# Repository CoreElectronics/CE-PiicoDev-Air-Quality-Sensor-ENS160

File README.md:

# PiicoDev® Air Quality Sensor ENS160

<!-- TODO update link URL with CE SKU -->
<!-- TODO update link title -->
<!-- TODO put image in Documents directory. Piicodev image 1500x1000 resize to 30% -> 450x300 -->

This is the hardware repo for the Core Electronics [PiicoDev Air Quality Sensor ENS160](https://core-electronics.com.au/catalog/product/view/sku/CE08560).

<!-- TODO populate below here from the tutorial -->

## License
This project is open source - please review the LICENSE.md file for further licensing information.

If you have any technical questions, or concerns about licensing, please contact technical support on the [Core Electronics forums](https://forum.core-electronics.com.au/).

## Attribution
<!-- TODO Confirm attribution eg
The hardware design of this module is influenced by the design from [Sparkfun](https://github.com/sparkfun/Qwiic_Capacitive_Touch_Slider_CAP1203).  -->

*\"PiicoDev\" and the PiicoDev logo are trademarks of Core Electronics Pty Ltd.*

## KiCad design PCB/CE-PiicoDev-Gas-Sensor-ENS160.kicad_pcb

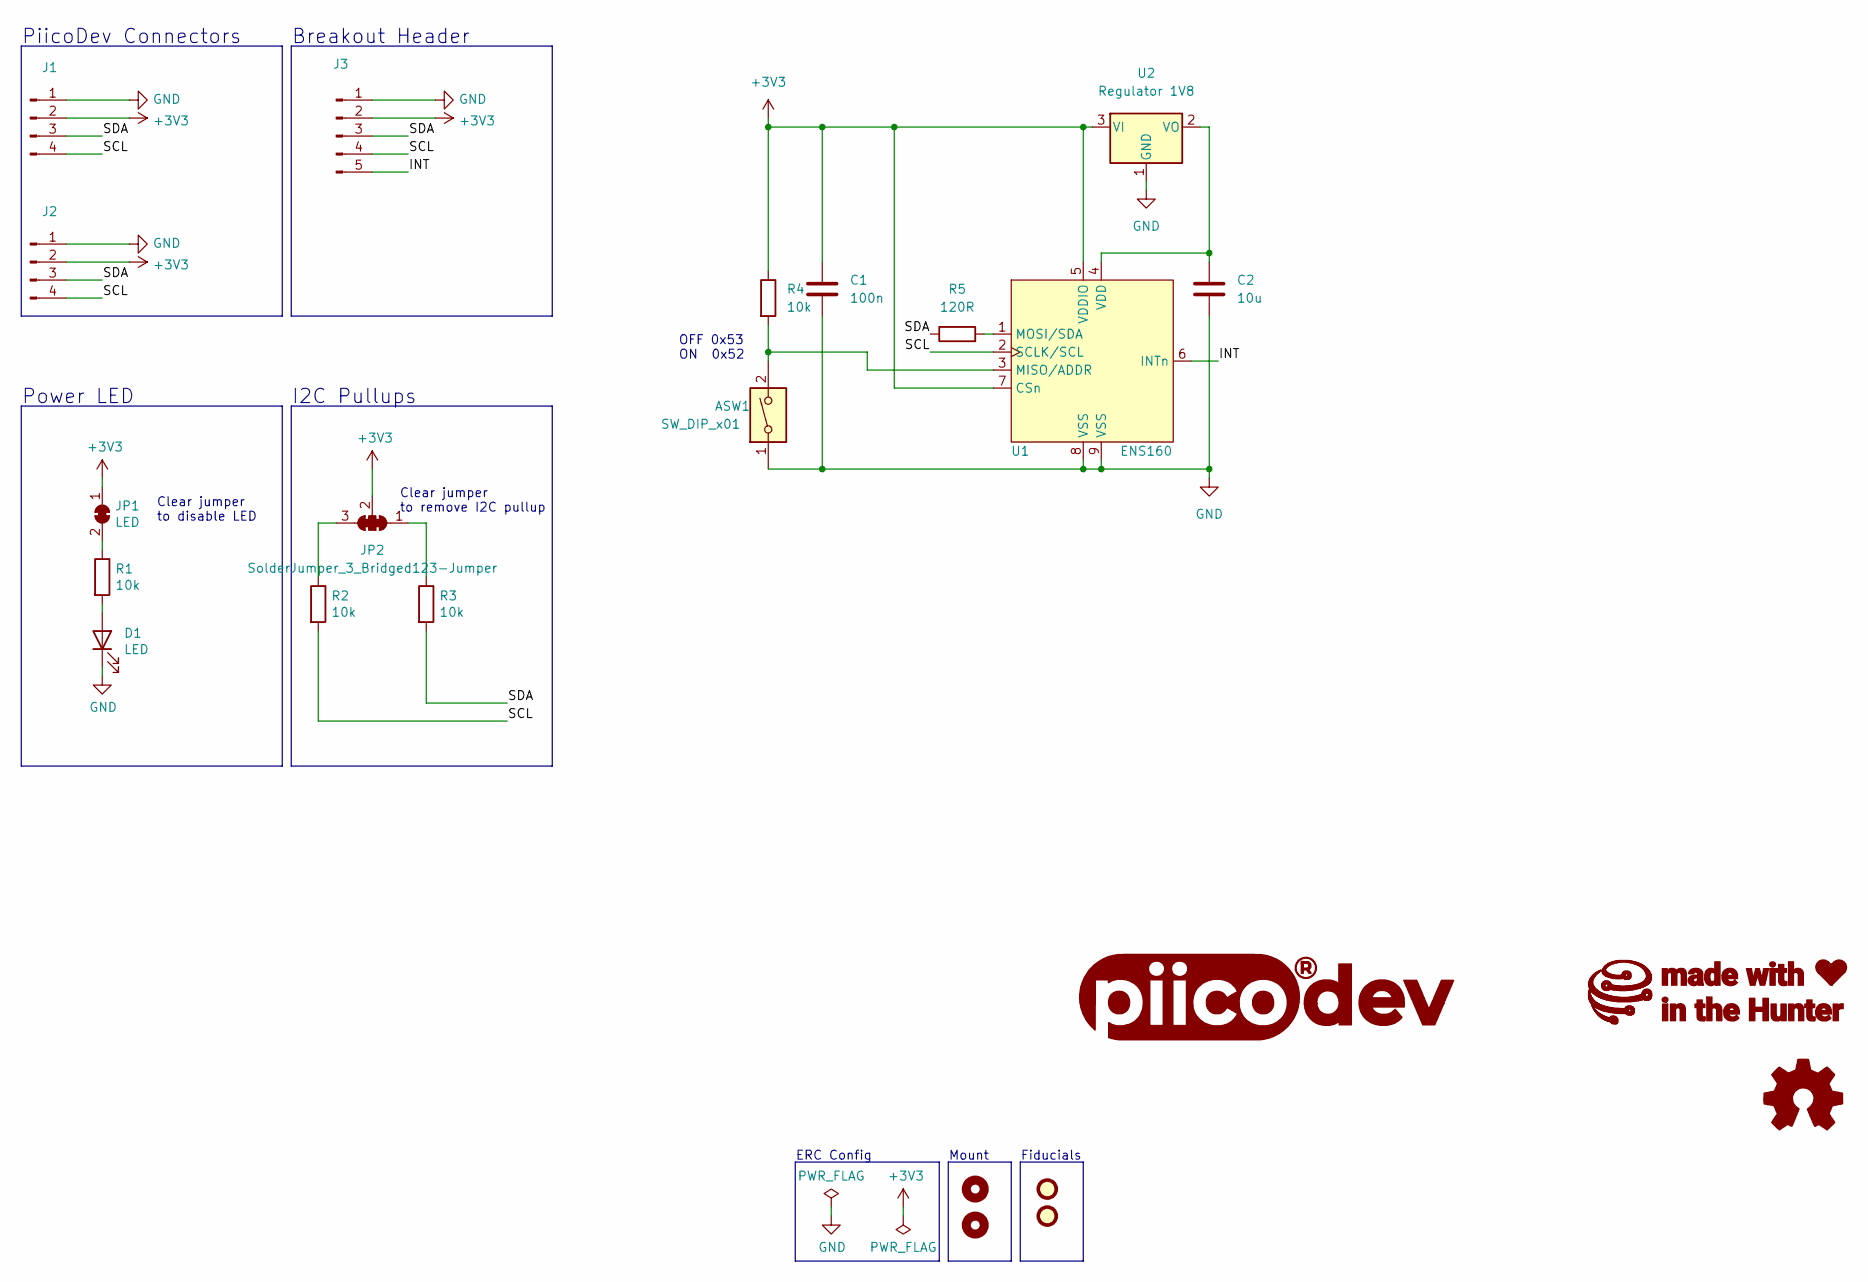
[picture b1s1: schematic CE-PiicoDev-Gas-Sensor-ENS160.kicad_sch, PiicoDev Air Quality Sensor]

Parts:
ASW1: SW_DIP_x01; SW_DIP_x01_Slide_CHS-01A1
C1: 100n; C_0402_1005Metric
C2: 10u; C_0603_1608Metric
D1: LED; LED_0603_1608Metric
FID1, FID2: Fiducial; Fiducial_1mm_Mask2mm
G1: LOGO_PiicoDev; piicodev_logo_14.2x3.4mm
G2: LOGO_CoreElectronics_no-text; CoreElectronics_logo_5mm
G3: LOGO_made-with-love; piicodev_logo_14.2x3.4mm
H1, H2: MountingHole; MountingHole_2.7mm_M2.5_PadClearance_1.2
J1, J2: JST_SH_SM04B-SRSS-TB_1x04-1MP_P1.00mm_Horizontal
J3: Conn_01x05_Male; PiicoDev_header_5pin
JP1: LED; SolderJumper-2_P1.3mm_Bridged_RoundedPad1.0x1.5mm
JP2: SolderJumper_3_Bridged123-Jumper; SolderJumper-3_P1.3mm_Closed_RoundedPad1.0x1.5mm_NumberLabe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
LOGO1: Logo_Open_Hardware_Small; oshw
R1, R2, R3, R4: 10k; R_0402_1005Metric
R5: 120R; R_0402_1005Metric
U1: ENS160; ScioSense_ENS160
U2: Regulator 1V8; SOT-23

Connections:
+3V3: C1.1, J1.2, J2.2, J3.2, JP1.1 (A), JP2.2 (C), R4.1, U1.5 (VDDIO), U1.7 (CSn), U2.3 (VI)
/INT: J3.5, U1.6 (INTn)
/SCL: J1.4, J2.4, J3.4, R2.2, U1.2 (SCLK/SCL)
/SDA: J1.3, J2.3, J3.3, R3.2, R5.1
GND: ASW1.1, C1.2, C2.2, D1.1 (K), J1.1, J2.1, J3.1, U1.8 (VSS), U1.9 (VSS), U2.1 (GND)
unnamed: C2.1, U1.4 (VDD), U2.2 (VO)
unnamed: D1.2 (A), R1.2
unnamed: JP1.2 (B), R1.1
unnamed: JP2.1 (A), R3.1
unnamed: JP2.3 (B), R2.1
unnamed: R5.2, U1.1 (MOSI/SDA)
unnamed: ASW1.2, R4.2, U1.3 (MISO/ADDR)

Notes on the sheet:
Breakout Header
Fiducials
I2C Pullups
Clear jumper to remove I2C pullup
ERC Config
OFF 0x53 ON 0x52
Power LED
Clear jumper to disable LED
Mount
PiicoDev Connectors

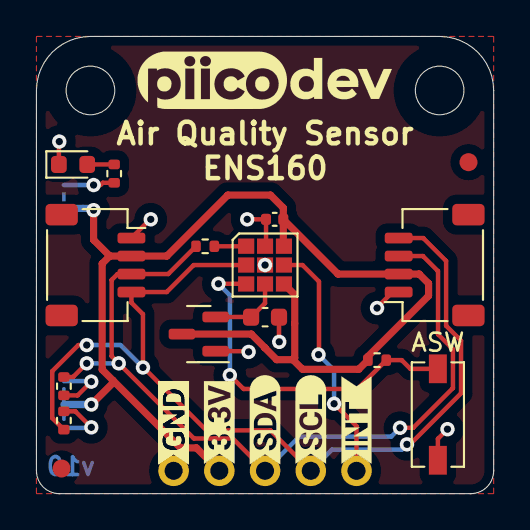
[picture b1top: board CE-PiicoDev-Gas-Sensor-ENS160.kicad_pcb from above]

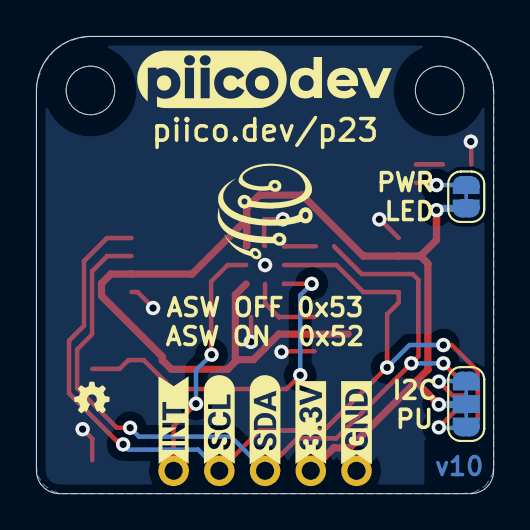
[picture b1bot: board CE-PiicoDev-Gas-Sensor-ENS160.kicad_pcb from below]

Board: 2 copper layers, 25.4 x 25.4 mm, 35 parts (10 on the bottom side), 12 nets.

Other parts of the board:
kibuzzard-6285E79D, kibuzzard-6285E79D#2: G***; kibuzzard-6285E79D
kibuzzard-6285E559, kibuzzard-6285E559#2: G***; kibuzzard-6285E559
kibuzzard-6285E568, kibuzzard-6285E568#2: G***; kibuzzard-6285E568
kibuzzard-6285E695, kibuzzard-6285E695#2, kibuzzard-6285E695#3: G***; kibuzzard-6285E695
kibuzzard-6285E748, kibuzzard-6285E748#2: G***; kibuzzard-6285E748

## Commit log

2022-05-04 Add PCB
2022-06-21 Change default I2C address
2022-07-25 v10 release
2022-08-10 Add plot directory
2022-10-07 Add datasheet

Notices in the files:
PCB/CE-PiicoDev-Gas-Sensor-ENS160.kicad_pcb:
License: CCASAv4.0 http://creativecommons.org/licenses/by-sa/4.0
